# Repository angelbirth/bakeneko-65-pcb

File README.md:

# Bakeneko 65 PCB

A 65% O-ring gasket mount keyboard.

## Features
 * Compatible with [Unified Daughterboard](https://github.com/ai03-2725/Unified-Daughterboard)
 * QMK Firmware
 * No switch LEDs and no underglow
 * All switches are south facing
 * Designed with KiCAD 5.1.6

## Supported Layouts

## Supported Switches
 * Cherry MX and clone switches

## Case
 * [Aluminum case](https://github.com/kkatano/bakeneko-65-case)

## Plate

 * [FR4 plate](https://github.com/kkatano/bakeneko-65-fr4-full-plate)
 * [FR4 half plate](https://github.com/kkatano/bakeneko-65-fr4-half-plate)

## BOM

TBU

## Firmware

TBU

## Lisence

Bakeneko 65 PCB is released under the MIT License.

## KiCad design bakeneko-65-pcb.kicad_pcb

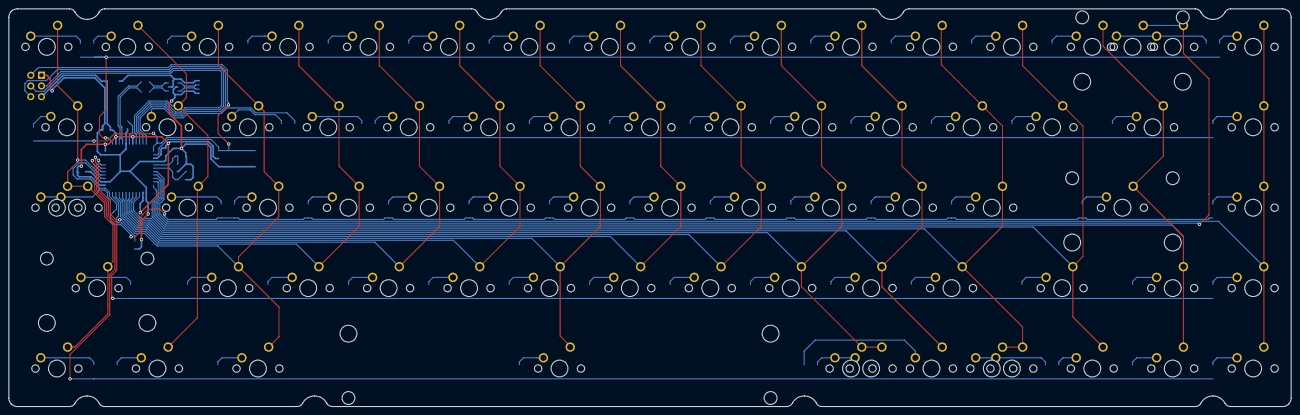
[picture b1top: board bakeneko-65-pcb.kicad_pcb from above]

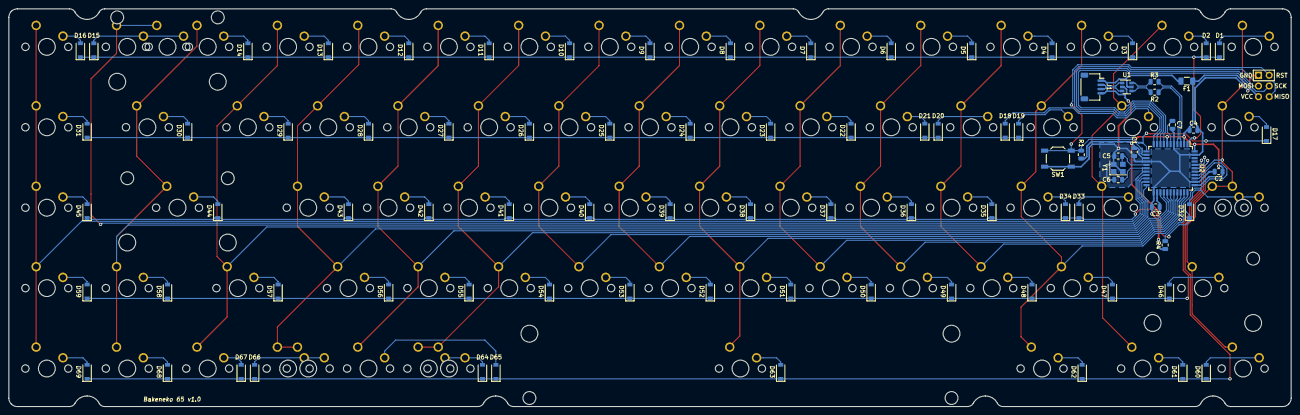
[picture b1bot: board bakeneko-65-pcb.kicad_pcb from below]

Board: 2 copper layers, 303.8 x 94.2 mm, 160 parts (87 on the bottom side), 107 nets.

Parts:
C1, C2, C3: 0.1u; C_0805_2012Metric
C4: 10u; C_0805_2012Metric
C5, C6: 22p; C_0805_2012Metric
C7: 1u; C_0805_2012Metric
D1, D2, D3, D4, D5, D6, D7, D8, D9, D10, D11, D12, D13, D14, D15, D16, D17, D18, D19, D20, D21, D22, D23, D24, D25, D26, D27, D28, D29, D30, D31, D32, D33, D34, D35, D36, D37, D38, D39, D40, D41, D42, D43, D44, D45, D46, D47, D48, D49, D50, D51, D52, D53, D54, D55, D56, D57, D58, D59, D60, D61, D62, D63, D64, D65, D66, D67, D68, D69: 1N4148; D_SOD-123
F1: 500mA; Fuse_1206_3216Metric
J1: JST SH 4-pin; JST_SH_SM04B-SRSS-TB_1x04-1MP_P1.00mm_Horizontal
J2: AVR-ISP-6; Reset_Pretty
MX1, MX2, MX3, MX4, MX5, MX6, MX7, MX8, MX9, MX10, MX11, MX12, MX13, MX14, MX15, MX16, MX19, MX20, MX21, MX22, MX23, MX24, MX25, MX26, MX27, MX28, MX29, MX30, MX32, MX35, MX36, MX37, MX38, MX39, MX40, MX41, MX42, MX43, MX44, MX45, MX47, MX49, MX50, MX51, MX52, MX53, MX54, MX55, MX56, MX57, MX58, MX60, MX61, MX66, MX67, MX68, MX69, MX70, MX71: 1u; MXOnly-1U-NoLED
MX17: 2u; MXOnly-2U-NoLED
MX18, MX31, MX72, MX73: 1.5u; MXOnly-1.5U-NoLED
MX33, MX62, MX63, MX64: 1.25u; MXOnly-1.25U-NoLED
MX34, MX59: 1.75u; MXOnly-1.75U-NoLED
MX46, MX48: 2.25u; MXOnly-2.25U-NoLED
MX65: 6.25u; MXOnly-6.25U-ReversedStabilizers-NoLED
R1, R4: 10k; R_0805_2012Metric
R2, R3: 22; R_0805_2012Metric
SW1: Reset; SW_SPST_TL3342
U1: USBLC6-2SC6; SOT-23-6
U2: ATmega32U4-AU; TQFP-44_10x10mm_P0.8mm
Y1: 16MHz; Crystal_SMD_3225-4Pin_3.2x2.5mm

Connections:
+5V: C1.1, C2.1, C3.1, C4.1, F1.1, J2.2, R1.2, U2.2, U2.7, U2.14, U2.24, U2.34, U2.44
/MCU_D+: R2.1, U2.4
/MCU_D-: R3.1, U2.3
COL0: MX1.2, MX18.2, MX33.2, MX34.2, MX48.2, MX62.2, U2.37
COL1: MX2.2, MX19.2, MX35.2, MX63.2, U2.8
COL2: MX3.2, MX20.2, MX36.2, MX49.2, MX64.2, U2.40
COL3: MX4.2, MX21.2, MX37.2, MX50.2, U2.32
COL4: MX5.2, MX22.2, MX38.2, MX51.2, U2.31
COL5: MX6.2, MX23.2, MX39.2, MX52.2, U2.30
COL6: MX7.2, MX24.2, MX40.2, MX53.2, MX65.2, U2.29
COL7: MX8.2, MX25.2, MX41.2, MX54.2, U2.28
COL8: MX9.2, MX26.2, MX42.2, MX55.2, U2.27
COL9: MX10.2, MX27.2, MX43.2, MX56.2, MX66.2, MX72.2, U2.26
COL10: MX11.2, MX28.2, MX44.2, MX57.2, MX67.2, U2.25
COL11: MX12.2, MX29.2, MX45.2, MX58.2, MX68.2, MX73.2, U2.22
COL12: MX13.2, MX30.2, MX59.2, MX69.2, U2.21
COL13: MX14.2, MX31.2, MX46.2, MX60.2, MX70.2, U2.20
COL14: MX15.2, MX17.2, U2.19
COL15: MX16.2, MX32.2, MX47.2, MX61.2, MX71.2, U2.18
D+: J1.3, U1.3
D-: J1.2, U1.1
ESD_D+: R2.2, U1.4
ESD_D-: R3.2, U1.6
GND: C1.2, C2.2, C3.2, C4.2, C5.1, C6.1, C7.2, J1.4, J2.6, R4.1, SW1.1, U1.2, U2.5, U2.15, U2.23, U2.35, U2.43, Y1.2, Y1.4
MISO: J2.1, U2.11
MOSI: J2.4, U2.10
unnamed: C7.1, U2.6
unnamed: D1.2, MX1.1
unnamed: D2.2, MX2.1
unnamed: D3.2, MX3.1
unnamed: D4.2, MX4.1
unnamed: D5.2, MX5.1
unnamed: D6.2, MX6.1
unnamed: D7.2, MX7.1
unnamed: D8.2, MX8.1
unnamed: D9.2, MX9.1
unnamed: D10.2, MX10.1
unnamed: D11.2, MX11.1
unnamed: D12.2, MX12.1
unnamed: D13.2, MX13.1
unnamed: D14.2, MX14.1
unnamed: D15.2, MX15.1, MX17.1
unnamed: D16.2, MX16.1
unnamed: D17.2, MX18.1
unnamed: D18.2, MX19.1
unnamed: D19.2, MX20.1
unnamed: D20.2, MX21.1
unnamed: D21.2, MX22.1
unnamed: D22.2, MX23.1
unnamed: D23.2, MX24.1
unnamed: D24.2, MX25.1
unnamed: D25.2, MX26.1
unnamed: D26.2, MX27.1
unnamed: D27.2, MX28.1
unnamed: D28.2, MX29.1
unnamed: D29.2, MX30.1
unnamed: D30.2, MX31.1
unnamed: D31.2, MX32.1
unnamed: D32.2, MX33.1, MX34.1
unnamed: D33.2, MX35.1
unnamed: D34.2, MX36.1
unnamed: D35.2, MX37.1
unnamed: D36.2, MX38.1
unnamed: D37.2, MX39.1
unnamed: D38.2, MX40.1
unnamed: D39.2, MX41.1
unnamed: D40.2, MX42.1
unnamed: D41.2, MX43.1
unnamed: D42.2, MX44.1
unnamed: D43.2, MX45.1
unnamed: D44.2, MX46.1
unnamed: D45.2, MX47.1
unnamed: D46.2, MX48.1
unnamed: D47.2, MX49.1
unnamed: D48.2, MX50.1
unnamed: D49.2, MX51.1
unnamed: D50.2, MX52.1
unnamed: D51.2, MX53.1
unnamed: D52.2, MX54.1
unnamed: D53.2, MX55.1
unnamed: D54.2, MX56.1
unnamed: D55.2, MX57.1
unnamed: D56.2, MX58.1
unnamed: D57.2, MX59.1
unnamed: D58.2, MX60.1
unnamed: D59.2, MX61.1
unnamed: D60.2, MX62.1
unnamed: D61.2, MX63.1
unnamed: D62.2, MX64.1
unnamed: D63.2, MX65.1
unnamed: D64.2, MX66.1, MX72.1
unnamed: D65.2, MX67.1
unnamed: D66.2, MX68.1, MX73.1
unnamed: D67.2, MX69.1
unnamed: D68.2, MX70.1
unnamed: D69.2, MX71.1
unnamed: R4.2, U2.33
RESET: J2.5, R1.1, SW1.2, U2.13
ROW0: D1.1, D2.1, D3.1, D4.1, D5.1, D6.1, D7.1, D8.1, D9.1, D10.1, D11.1, D12.1, D13.1, D14.1, D15.1, D16.1, U2.1
ROW1: D17.1, D18.1, D19.1, D20.1, D21.1, D22.1, D23.1, D24.1, D25.1, D26.1, D27.1, D28.1, D29.1, D30.1, D31.1, U2.12
ROW2: D32.1, D33.1, D34.1, D35.1, D36.1, D37.1, D38.1, D39.1, D40.1, D41.1, D42.1, D43.1, D44.1, D45.1, U2.36
ROW3: D46.1, D47.1, D48.1, D49.1, D50.1, D51.1, D52.1, D53.1, D54.1, D55.1, D56.1, D57.1, D58.1, D59.1, U2.39
ROW4: D60.1, D61.1, D62.1, D63.1, D64.1, D65.1, D66.1, D67.1, D68.1, D69.1, U2.38
SCK: J2.3, U2.9
VBUS: F1.2, J1.1, U1.5
XTAL1: C6.2, U2.17, Y1.1
XTAL2: C5.2, U2.16, Y1.3

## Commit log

2020-07-31 Create project
2020-08-02 Update PCB
2020-08-10 Modify outline
2020-08-15 Add new stuff
2020-08-15 Fix backspace key
